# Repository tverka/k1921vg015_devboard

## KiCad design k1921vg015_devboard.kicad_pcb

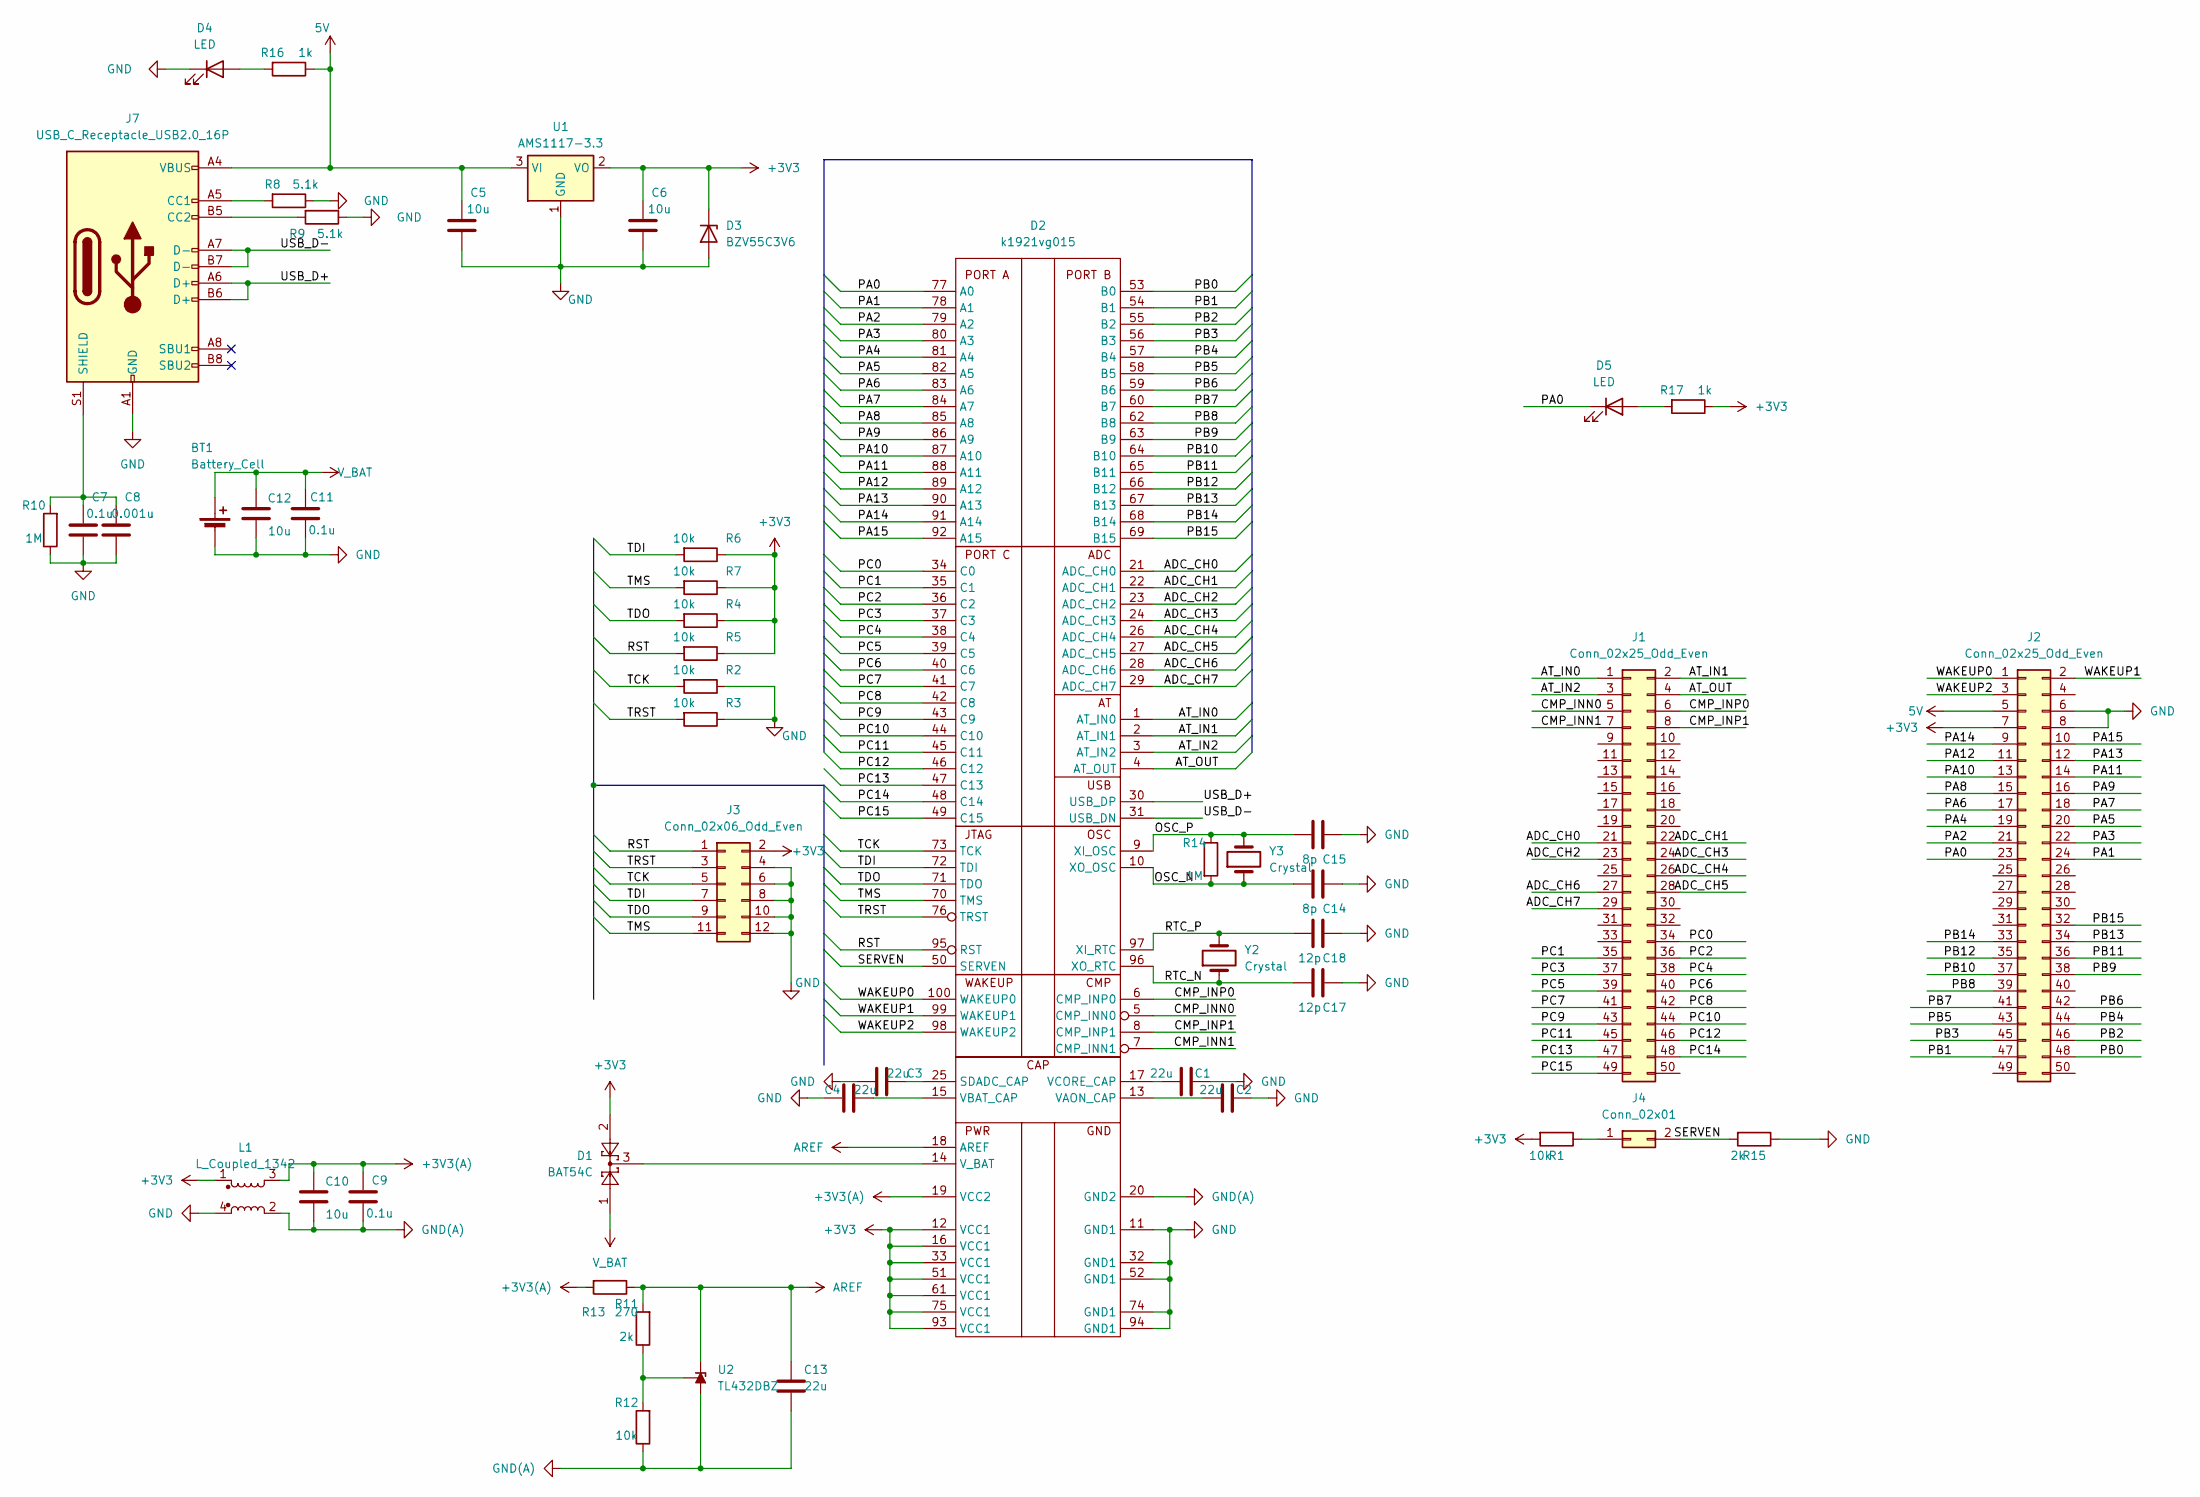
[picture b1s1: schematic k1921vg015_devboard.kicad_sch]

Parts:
BT1: Battery_Cell; BatteryHolder_Keystone_1058_1x2032
C1, C2, C3, C4, C13: 22u; C_0805_2012Metric_Pad1.18x1.45mm_HandSolder
C5, C6, C10, C12: 10u; C_0805_2012Metric_Pad1.18x1.45mm_HandSolder
C7, C9, C11: 0.1u; C_0805_2012Metric_Pad1.18x1.45mm_HandSolder
C8: 0.001u; C_0805_2012Metric_Pad1.18x1.45mm_HandSolder
C14, C15: 8p; C_0805_2012Metric_Pad1.18x1.45mm_HandSolder
C17, C18: 12p; C_0805_2012Metric_Pad1.18x1.45mm_HandSolder
D1: BAT54C; SOT-23
D2: k1921vg015; LQFP-100_14x14mm_P0.5mm
D3: BZV55C3V6; D_MiniMELF_Handsoldering
D4, D5: LED; LED_1206_3216Metric_Pad1.42x1.75mm_HandSolder
J1, J2: Conn_02x25_Odd_Even; PinHeader_2x25_P2.54mm_Vertical
J3: Conn_02x06_Odd_Even; PinHeader_2x06_P2.54mm_Vertical
J4: Conn_02x01; PinHeader_2x01_P2.54mm_Vertical
J7: USB_C_Receptacle_USB2.0_16P; USB_C_Receptacle_GCT_USB4135-GF-A_6P_TopMnt_Horizontal
L1: L_Coupled_1342; L_CommonModeChoke_Murata_DLW5BTMxxxSQ2x_5x5mm
R1, R2, R3, R4, R5, R6, R7, R12: 10k; R_0805_2012Metric_Pad1.20x1.40mm_HandSolder
R8, R9: 5.1k; R_0805_2012Metric_Pad1.20x1.40mm_HandSolder
R10, R14: 1M; R_0805_2012Metric_Pad1.20x1.40mm_HandSolder
R11, R15: 2k; R_0805_2012Metric_Pad1.20x1.40mm_HandSolder
R13: 270; R_0805_2012Metric_Pad1.20x1.40mm_HandSolder
R16, R17: 1k; R_0805_2012Metric_Pad1.20x1.40mm_HandSolder
U1: AMS1117-3.3; SOT-223-3_TabPin2
U2: TL432DBZ; SOT-23
Y2: Crystal; Crystal_SMD_MicroCrystal_CM9V-T1A-2Pin_1.6x1.0mm_HandSolder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
Y3: Crystal; Oscillator_SMD_Abracon_ASE-4Pin_3.2x2.5mm_HandSoldering

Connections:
5V: C5.1, J2.5, J7.A4 (VBUS), J7.A9 (VBUS), J7.B4 (VBUS), J7.B9 (VBUS), R16.1, U1.3 (VI)
+3V3: C6.1, D1.2, D2.12 (VCC1), D2.16 (VCC1), D2.33 (VCC1), D2.51 (VCC1), D2.61 (VCC1), D2.75 (VCC1), D2.93 (VCC1), D3.1 (K), J2.7, J3.2, L1.1, R1.2, R4.1, R5.1, R6.1, R7.1, R17.1, U1.2 (VO); also elsewhere on the board
+3V3(A): C9.1, C10.1, D2.19 (VCC2), L1.3, R13.2
/ADC_CH0: D2.21 (ADC_CH0), J1.21
/ADC_CH1: D2.22 (ADC_CH1), J1.22
/ADC_CH2: D2.23 (ADC_CH2), J1.23
/ADC_CH3: D2.24 (ADC_CH3), J1.24
/ADC_CH4: D2.26 (ADC_CH4), J1.26
/ADC_CH5: D2.27 (ADC_CH5), J1.28
/ADC_CH6: D2.28 (ADC_CH6), J1.27
/ADC_CH7: D2.29 (ADC_CH7), J1.29
/AT_IN0: D2.1 (AT_IN0), J1.1
/AT_IN1: D2.2 (AT_IN1), J1.2
/AT_IN2: D2.3 (AT_IN2), J1.3
/AT_OUT: D2.4 (AT_OUT), J1.4
/CMP_INN0: D2.5 (CMP_INN0), J1.5
/CMP_INN1: D2.7 (CMP_INN1), J1.7
/CMP_INP0: D2.6 (CMP_INP0), J1.6
/CMP_INP1: D2.8 (CMP_INP1), J1.8
/OSC_N: C14.1, D2.10 (XO_OSC), R14.2, Y3.1
/OSC_P: C15.1, D2.9 (XI_OSC), R14.1, Y3.3
/PA0: D2.77 (A0), D5.1 (K), J2.23
/PA1: D2.78 (A1), J2.24
/PA2: D2.79 (A2), J2.21
/PA3: D2.80 (A3), J2.22
/PA4: D2.81 (A4), J2.19
/PA5: D2.82 (A5), J2.20
/PA6: D2.83 (A6), J2.17
/PA7: D2.84 (A7), J2.18
/PA8: D2.85 (A8), J2.15
/PA9: D2.86 (A9), J2.16
/PA10: D2.87 (A10), J2.13
/PA11: D2.88 (A11), J2.14
/PA12: D2.89 (A12), J2.11
/PA13: D2.90 (A13), J2.12
/PA14: D2.91 (A14), J2.9
/PA15: D2.92 (A15), J2.10
/PB0: D2.53 (B0), J2.48
/PB1: D2.54 (B1), J2.47
/PB2: D2.55 (B2), J2.46
/PB3: D2.56 (B3), J2.45
/PB4: D2.57 (B4), J2.44
/PB5: D2.58 (B5), J2.43
/PB6: D2.59 (B6), J2.42
/PB7: D2.60 (B7), J2.41
/PB8: D2.62 (B8), J2.39
/PB9: D2.63 (B9), J2.38
/PB10: D2.64 (B10), J2.37
/PB11: D2.65 (B11), J2.36
/PB12: D2.66 (B12), J2.35
/PB13: D2.67 (B13), J2.34
/PB14: D2.68 (B14), J2.33
/PB15: D2.69 (B15), J2.32
/PC0: D2.34 (C0), J1.34
/PC1: D2.35 (C1), J1.35
/PC2: D2.36 (C2), J1.36
/PC3: D2.37 (C3), J1.37
/PC4: D2.38 (C4), J1.38
/PC5: D2.39 (C5), J1.39
/PC6: D2.40 (C6), J1.40
/PC7: D2.41 (C7), J1.41
/PC8: D2.42 (C8), J1.42
/PC9: D2.43 (C9), J1.43
/PC10: D2.44 (C10), J1.44
/PC11: D2.45 (C11), J1.45
/PC12: D2.46 (C12), J1.46
/PC13: D2.47 (C13), J1.47
/PC14: D2.48 (C14), J1.48
/PC15: D2.49 (C15), J1.49
/RST: D2.95 (RST), J3.1, R5.2; also elsewhere on the board
/RTC_N: C17.1, D2.96 (XO_RTC), Y2.1
/RTC_P: C18.1, D2.97 (XI_RTC), Y2.2
/SERVEN: D2.50 (SERVEN), J4.2, R15.2; also elsewhere on the board
/TCK: D2.73 (TCK), J3.5, R2.2; also elsewhere on the board
/TDI: D2.72 (TDI), J3.7, R6.2; also elsewhere on the board
/TDO: D2.71 (TDO), J3.9, R4.2; also elsewhere on the board
/TMS: D2.70 (TMS), J3.11, R7.2; also elsewhere on the board
/TRST: D2.76 (TRST), J3.3, R3.2; also elsewhere on the board
/USB_D+: D2.30 (USB_DP), J7.A6 (D+), J7.B6 (D+)
/USB_D-: D2.31 (USB_DN), J7.A7 (D-), J7.B7 (D-)
/WAKEUP0: D2.100 (WAKEUP0), J2.1
/WAKEUP1: D2.99 (WAKEUP1), J2.2
/WAKEUP2: D2.98 (WAKEUP2), J2.3
AREF: C13.1, D2.18 (AREF), R11.2, R13.1, U2.2 (K)
GND: BT1.2 (-), C1.2, C2.2, C3.2, C4.2, C5.2, C6.2, C7.2, C8.2, C11.2, C12.2, C14.2, C15.2, C17.2, C18.2, D2.11 (GND1), D2.32 (GND1), D2.52 (GND1), D2.74 (GND1), D2.94 (GND1), D3.2 (A), D4.1 (K), J2.6, J2.8, J3.4, J3.6, J3.8, J3.10, J3.12, J7.A1 (GND), J7.A12 (GND), J7.B1 (GND), J7.B12 (GND), L1.4, R2.1, R3.1, R8.1, R9.1, R10.1, R15.1, U1.1 (GND); also elsewhere on the board
GND(A): C9.2, C10.2, C13.2, D2.20 (GND2), L1.2, R12.1, U2.3 (A)
unnamed: C3.1, D2.25 (SDADC_CAP)
unnamed: C2.1, D2.13 (VAON_CAP)
unnamed: C4.1, D2.15 (VBAT_CAP)
unnamed: C1.1, D2.17 (VCORE_CAP)
unnamed: D1.3, D2.14 (V_BAT)
unnamed: D4.2 (A), R16.2
unnamed: D5.2 (A), R17.2
unnamed 93: J4.1, R1.1; also elsewhere on the board
unnamed: J7.A5 (CC1), R8.2
unnamed: J7.B5 (CC2), R9.2
unnamed: C7.1, C8.1, J7.S1 (SHIELD), R10.2
unnamed: R11.1, R12.2, U2.1 (REF)
V_BAT: BT1.1 (+), C11.1, C12.1, D1.1

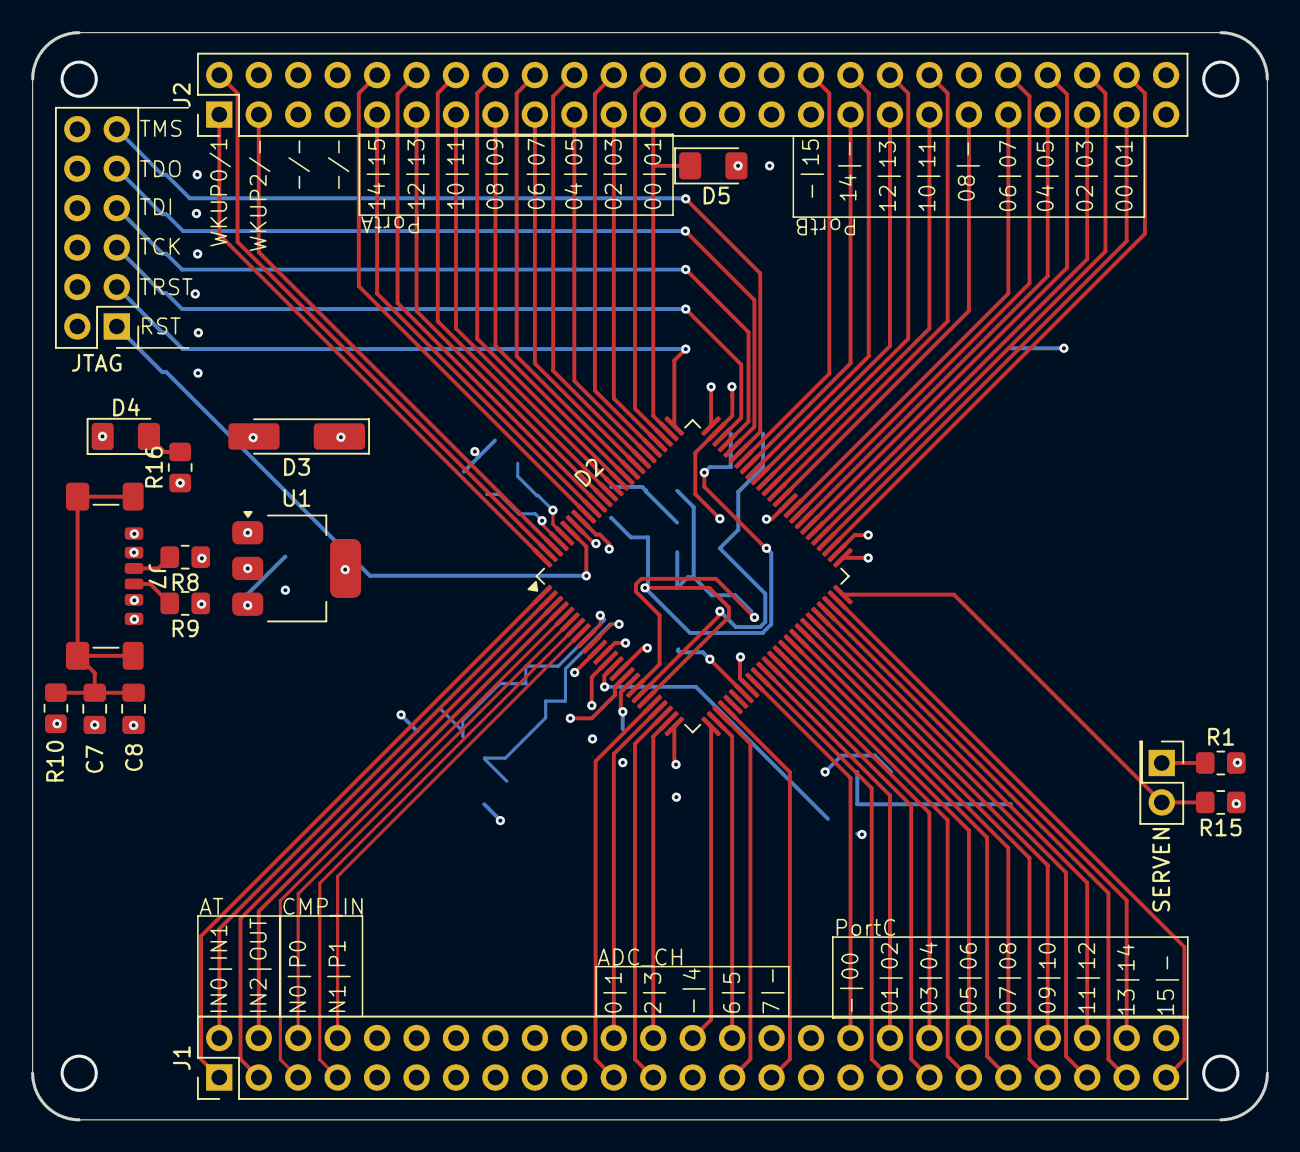
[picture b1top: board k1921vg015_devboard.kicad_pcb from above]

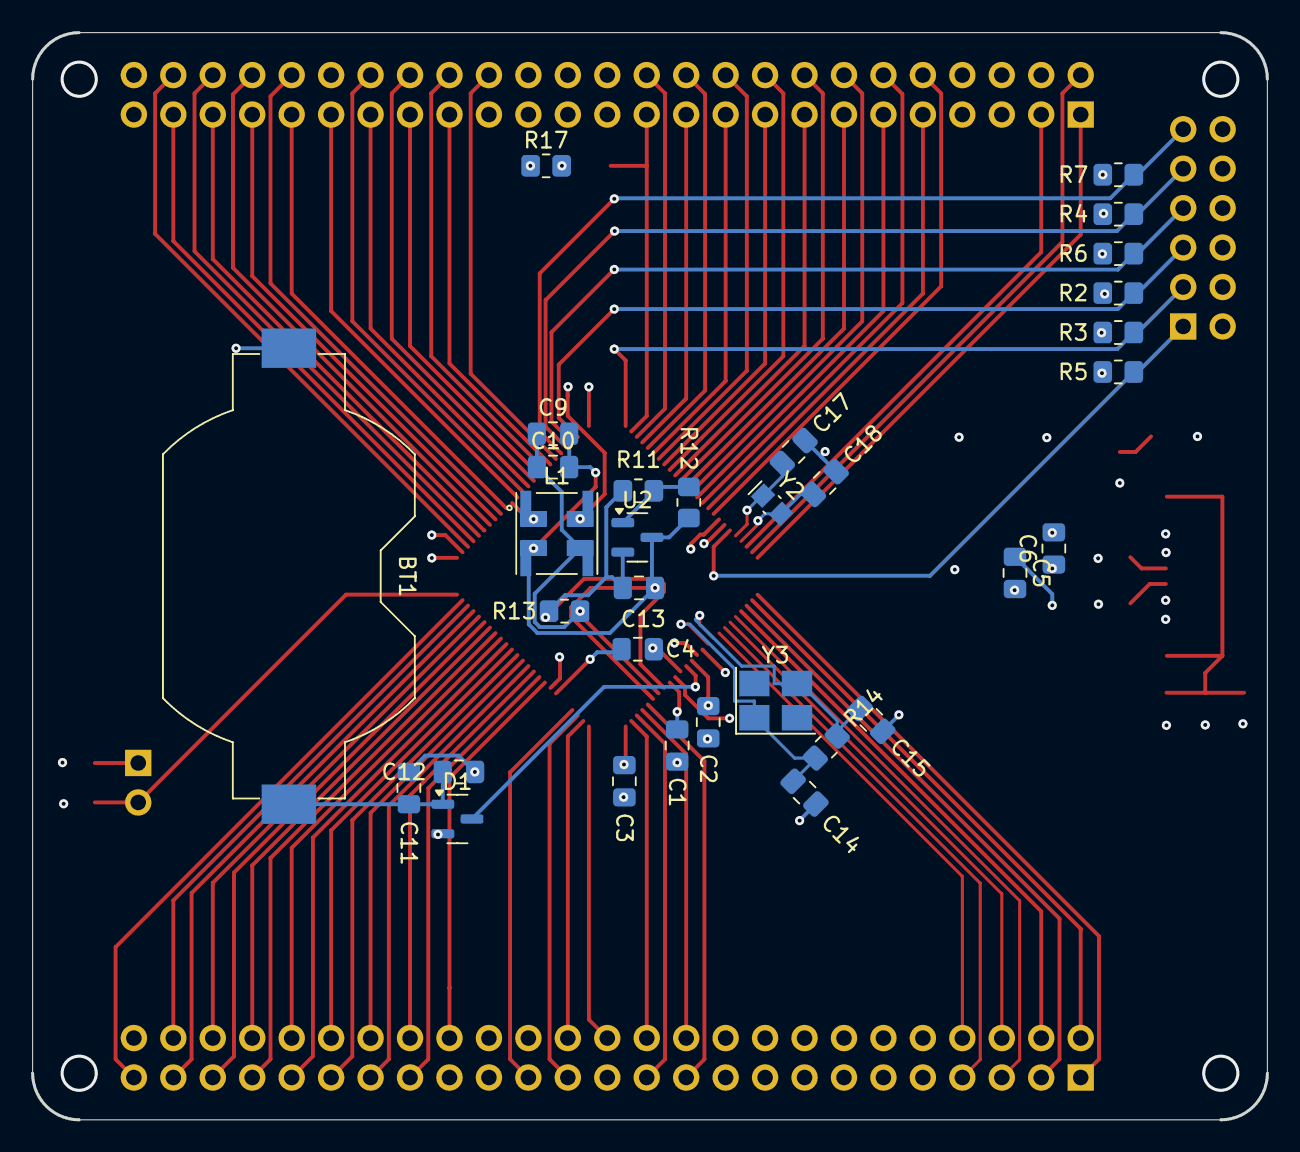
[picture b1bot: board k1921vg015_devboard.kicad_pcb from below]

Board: 4 copper layers, 79.5 x 70.0 mm, 50 parts (32 on the bottom side), 97 nets.

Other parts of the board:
JTAG: Conn_02x06_Odd_Even; PinHeader_2x06_P2.54mm_Vertical
SERVEN: Conn_02x01; PinHeader_2x01_P2.54mm_Vertical

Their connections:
+3V3: JTAG.2; also elsewhere on the board
/RST: JTAG.1; also elsewhere on the board
/SERVEN: SERVEN.2; also elsewhere on the board
/TCK: JTAG.5; also elsewhere on the board
/TDI: JTAG.7; also elsewhere on the board
/TDO: JTAG.9; also elsewhere on the board
/TMS: JTAG.11; also elsewhere on the board
/TRST: JTAG.3; also elsewhere on the board
GND: JTAG.4, JTAG.6, JTAG.8, JTAG.10, JTAG.12; also elsewhere on the board
unnamed 93: SERVEN.1; also elsewhere on the board

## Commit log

2025-04-21 add silkscreen
